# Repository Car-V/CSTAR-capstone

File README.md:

# CSTAR-capstone
Concrete Sounding Tool Automated Robot for EECE4792 Capstone 2

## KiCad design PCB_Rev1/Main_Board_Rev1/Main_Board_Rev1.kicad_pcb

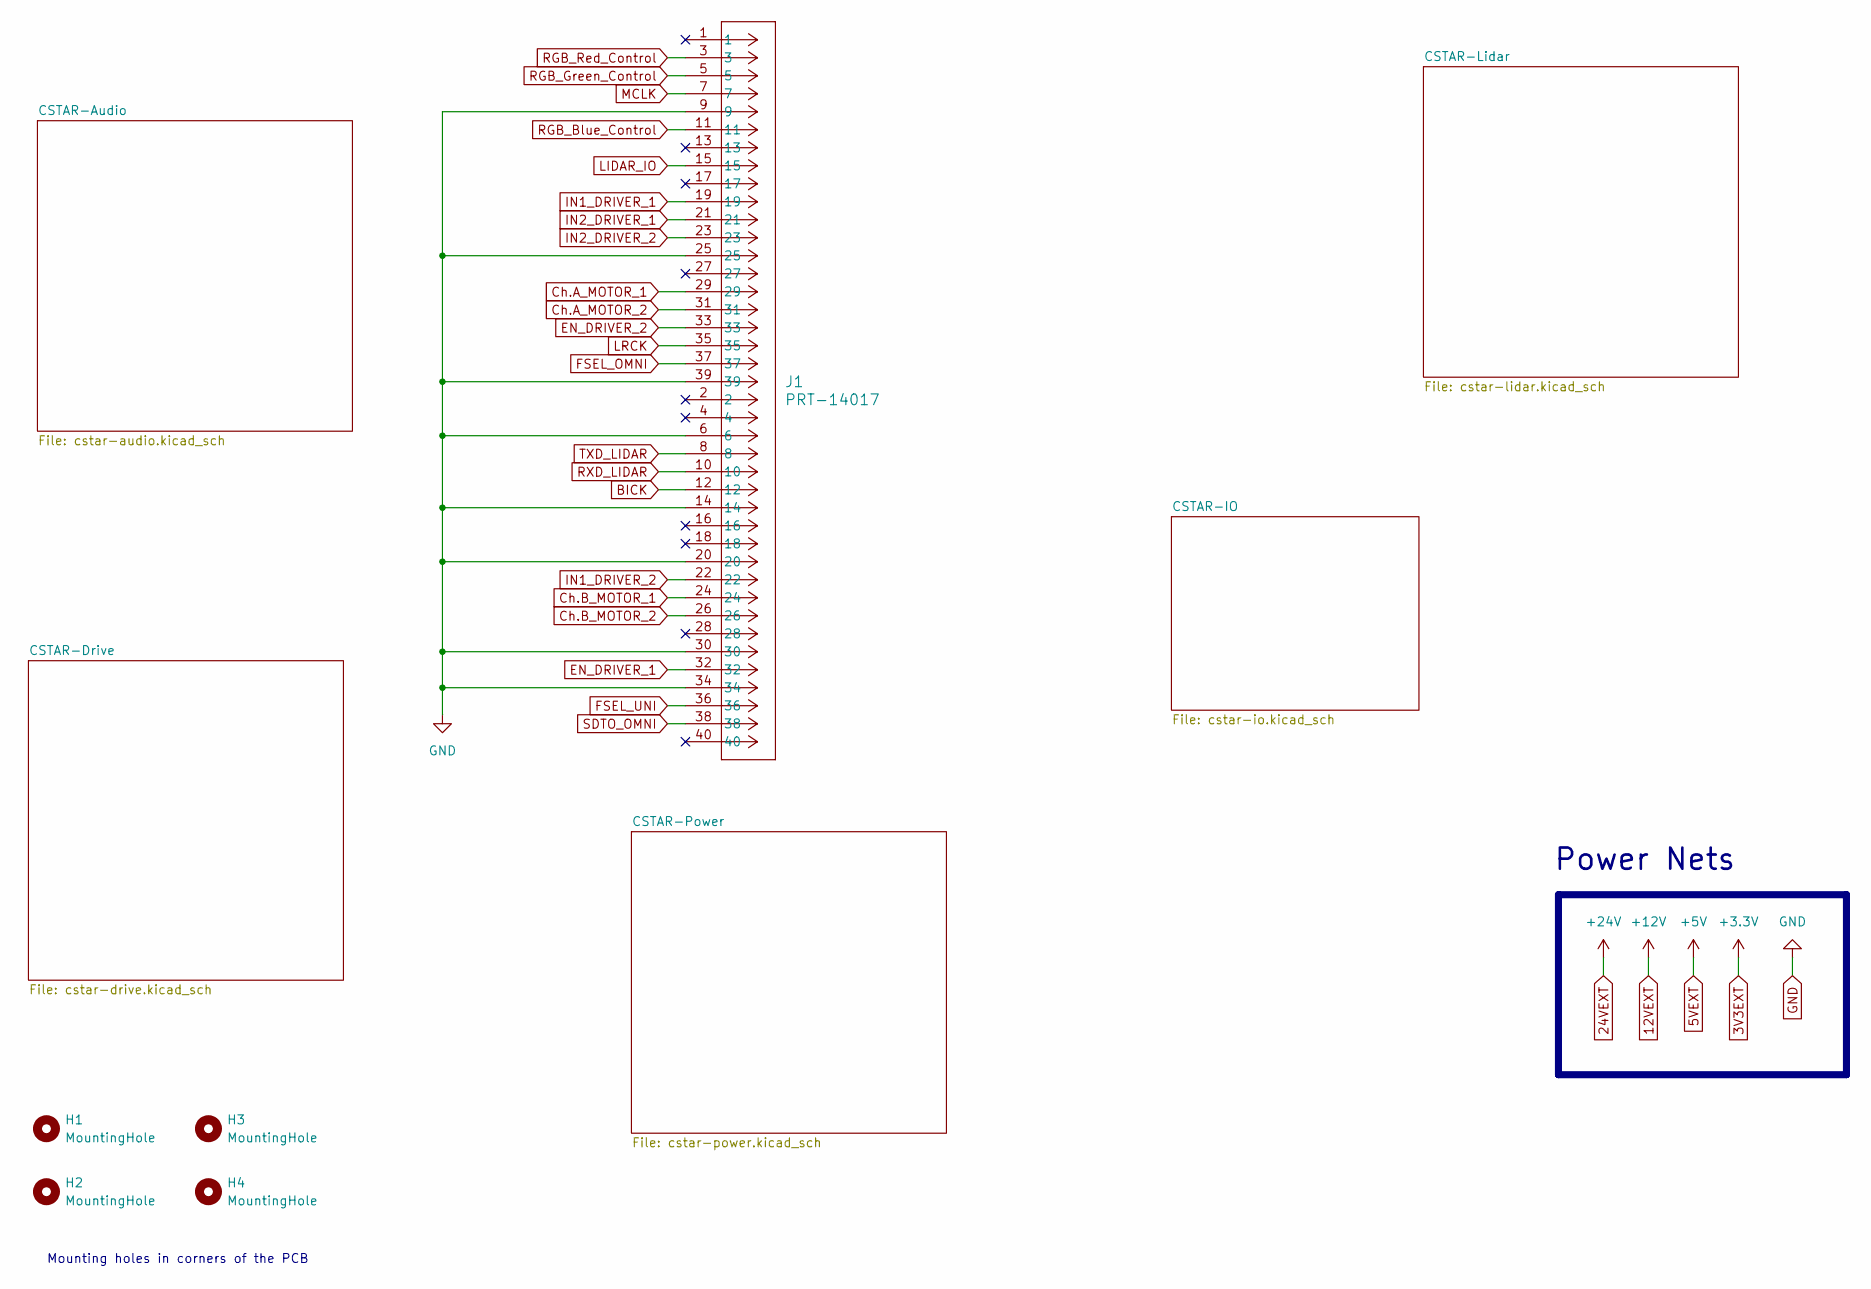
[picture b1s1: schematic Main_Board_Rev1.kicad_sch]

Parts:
H1, H2, H3, H4: MountingHole; MountingHole_5.3mm_M5_DIN965_Pad
J1: PRT-14017; RPiConnector; LCSC C2859067

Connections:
BICK: J1.12; also elsewhere on the board
Ch.A_MOTOR_1: J1.29; also elsewhere on the board
Ch.A_MOTOR_2: J1.31; also elsewhere on the board
Ch.B_MOTOR_1: J1.24; also elsewhere on the board
Ch.B_MOTOR_2: J1.26; also elsewhere on the board
EN_DRIVER_1: J1.32; also elsewhere on the board
EN_DRIVER_2: J1.33; also elsewhere on the board
FSEL_OMNI: J1.37; also elsewhere on the board
FSEL_UNI: J1.36; also elsewhere on the board
GND: J1.6, J1.9, J1.14, J1.20, J1.25, J1.30, J1.34, J1.39; also elsewhere on the board
IN1_DRIVER_1: J1.19; also elsewhere on the board
IN1_DRIVER_2: J1.22; also elsewhere on the board
IN2_DRIVER_1: J1.21; also elsewhere on the board
IN2_DRIVER_2: J1.23; also elsewhere on the board
LIDAR_IO: J1.15; also elsewhere on the board
LRCK: J1.35; also elsewhere on the board
MCLK: J1.7; also elsewhere on the board
RGB_Blue_Control: J1.11; also elsewhere on the board
RGB_Green_Control: J1.5; also elsewhere on the board
RGB_Red_Control: J1.3; also elsewhere on the board
RXD_LIDAR: J1.10; also elsewhere on the board
SDTO_OMNI: J1.38; also elsewhere on the board
TXD_LIDAR: J1.8; also elsewhere on the board

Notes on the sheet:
Power Nets
Mounting holes in corners of the PCB

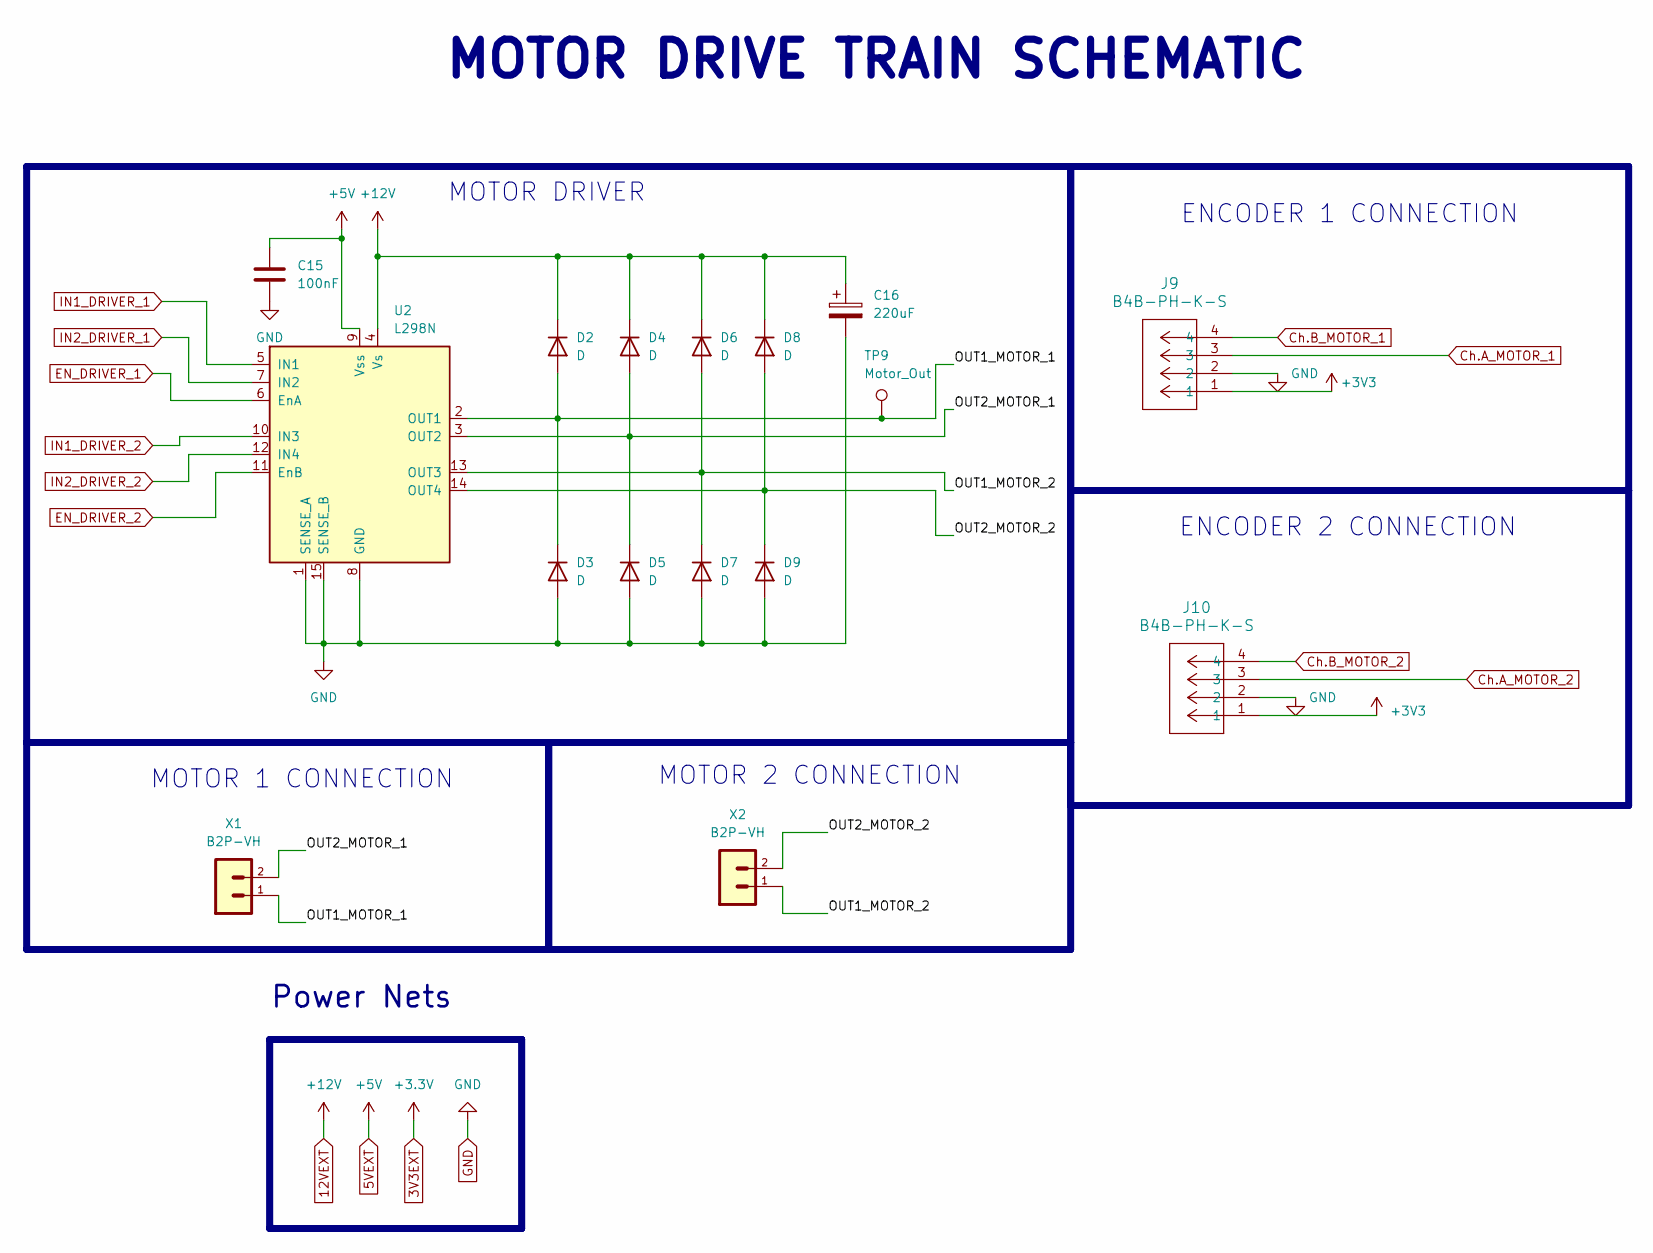
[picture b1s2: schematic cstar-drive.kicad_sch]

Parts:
C15: 100nF; C_0805_2012Metric; LCSC C520083
C16: 220uF; Cap_Polarized_220uF; LCSC C88729
D2, D3, D4, D5, D6, D7, D8, D9: D; Diode_1N4007; LCSC C516593
J9, J10: B4B-PH-K-S; B4B_PH_K_S; LCSC C305985
TP9: Motor_Out; TestPoint_Pad_D2.0mm
U2: L298N; TO-220-15_P2.54x2.54mm_StaggerOdd_Lead4.58mm_Vertical; LCSC C19922
X1, X2: B2P-VH; LCSC C160315

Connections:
5VEXT: C15.1, U2.9 (Vss); also elsewhere on the board
12VEXT: C16.1, D2.1 (K), D4.1 (K), D6.1 (K), D8.1 (K), U2.4 (Vs); also elsewhere on the board
+3V3: J9.1, J10.1; also elsewhere on the board
/CSTAR-Drive/OUT1_MOTOR_1: D2.2 (A), D3.1 (K), TP9.1, U2.2 (OUT1), X1.1
/CSTAR-Drive/OUT1_MOTOR_2: D6.2 (A), D7.1 (K), U2.13 (OUT3), X2.1
/CSTAR-Drive/OUT2_MOTOR_1: D4.2 (A), D5.1 (K), U2.3 (OUT2), X1.2
/CSTAR-Drive/OUT2_MOTOR_2: D8.2 (A), D9.1 (K), U2.14 (OUT4), X2.2
Ch.A_MOTOR_1: J9.3; also elsewhere on the board
Ch.A_MOTOR_2: J10.3; also elsewhere on the board
Ch.B_MOTOR_1: J9.4; also elsewhere on the board
Ch.B_MOTOR_2: J10.4; also elsewhere on the board
EN_DRIVER_1: U2.6 (EnA); also elsewhere on the board
EN_DRIVER_2: U2.11 (EnB); also elsewhere on the board
GND: C15.2, C16.2, D3.2 (A), D5.2 (A), D7.2 (A), D9.2 (A), J9.2, J10.2, U2.1 (SENSE_A), U2.8 (GND), U2.15 (SENSE_B); also elsewhere on the board
IN1_DRIVER_1: U2.5 (IN1); also elsewhere on the board
IN1_DRIVER_2: U2.10 (IN3); also elsewhere on the board
IN2_DRIVER_1: U2.7 (IN2); also elsewhere on the board
IN2_DRIVER_2: U2.12 (IN4); also elsewhere on the board

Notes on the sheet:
MOTOR 2 CONNECTION
Power Nets
MOTOR 1 CONNECTION
MOTOR DRIVER
ENCODER 1 CONNECTION
ENCODER 2 CONNECTION
MOTOR DRIVE TRAIN SCHEMATIC

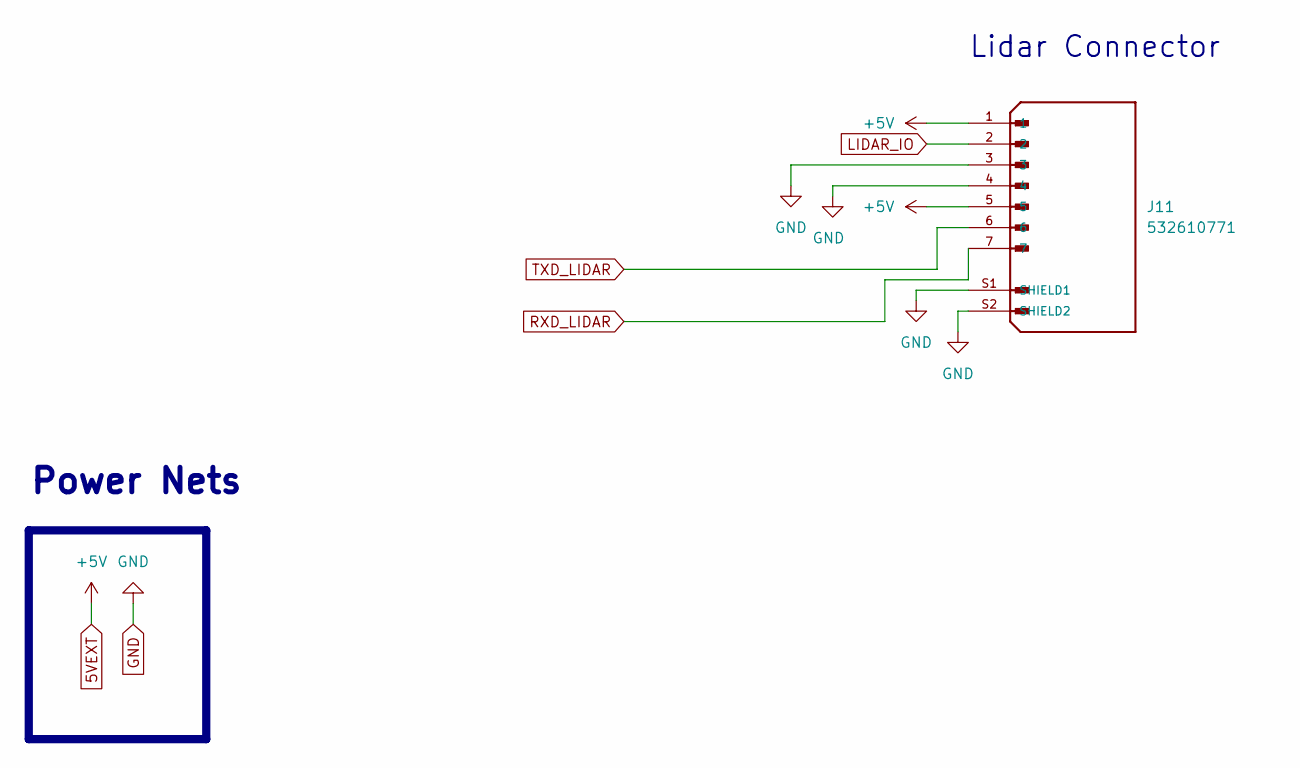
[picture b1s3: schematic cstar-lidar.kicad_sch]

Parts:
J11: 532610771; MOLEX_connector; PARTREV J; DigiKey_Part_Number WM7625TR-ND

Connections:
5VEXT: J11.1, J11.5; also elsewhere on the board
GND: J11.3, J11.4, J11.S1 (SHIELD1), J11.S2 (SHIELD2); also elsewhere on the board
LIDAR_IO: J11.2; also elsewhere on the board
RXD_LIDAR: J11.7; also elsewhere on the board
TXD_LIDAR: J11.6; also elsewhere on the board

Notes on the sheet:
Lidar Connector
Power Nets

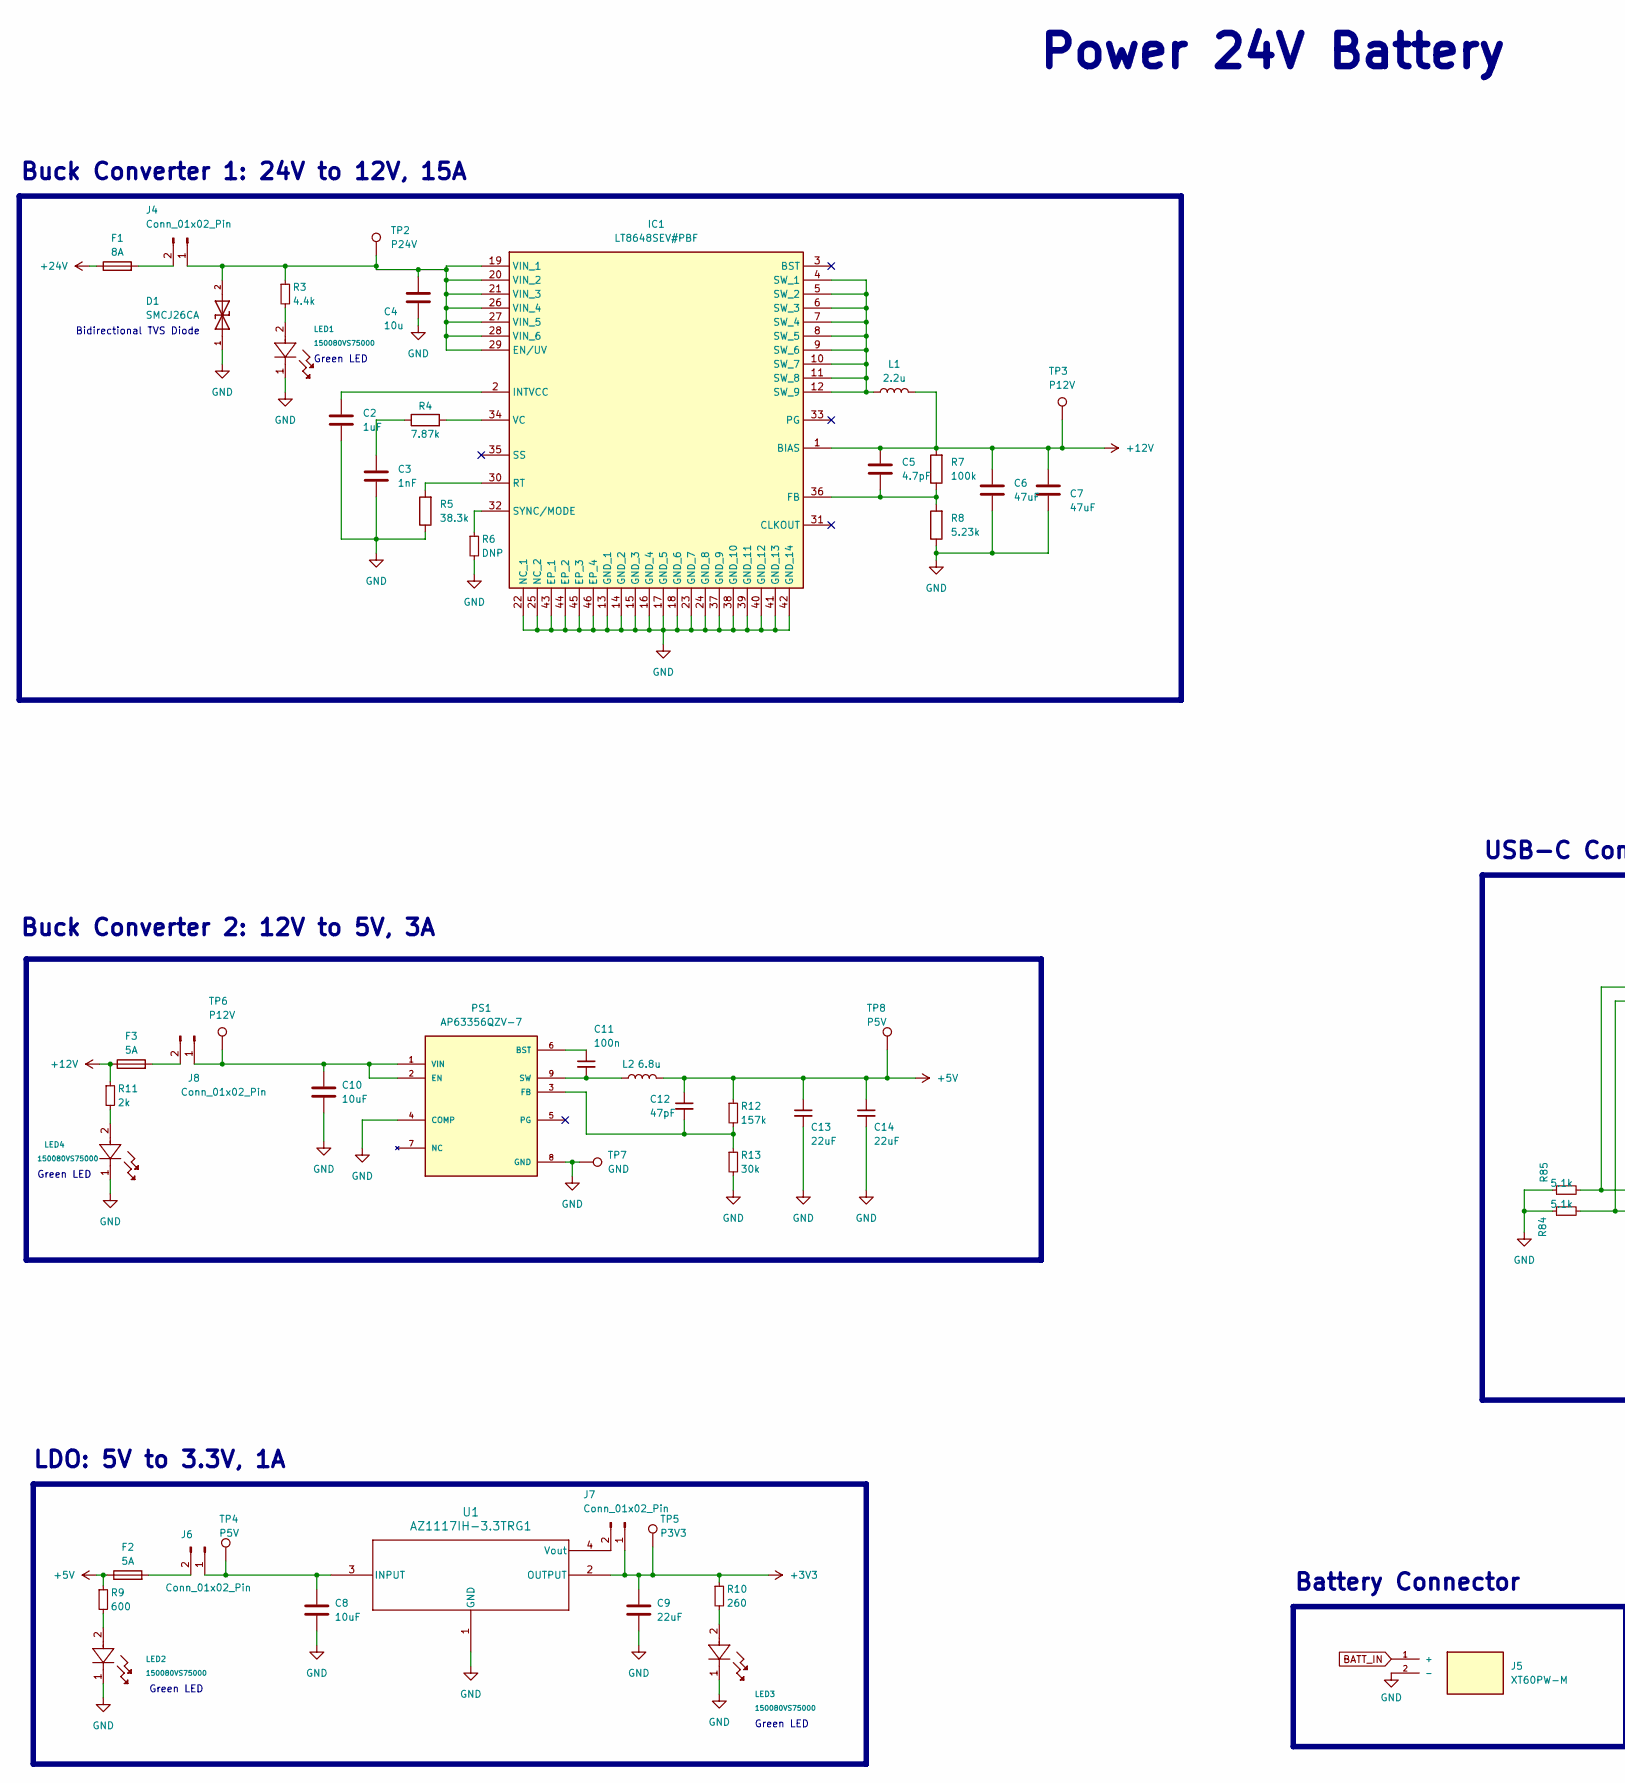
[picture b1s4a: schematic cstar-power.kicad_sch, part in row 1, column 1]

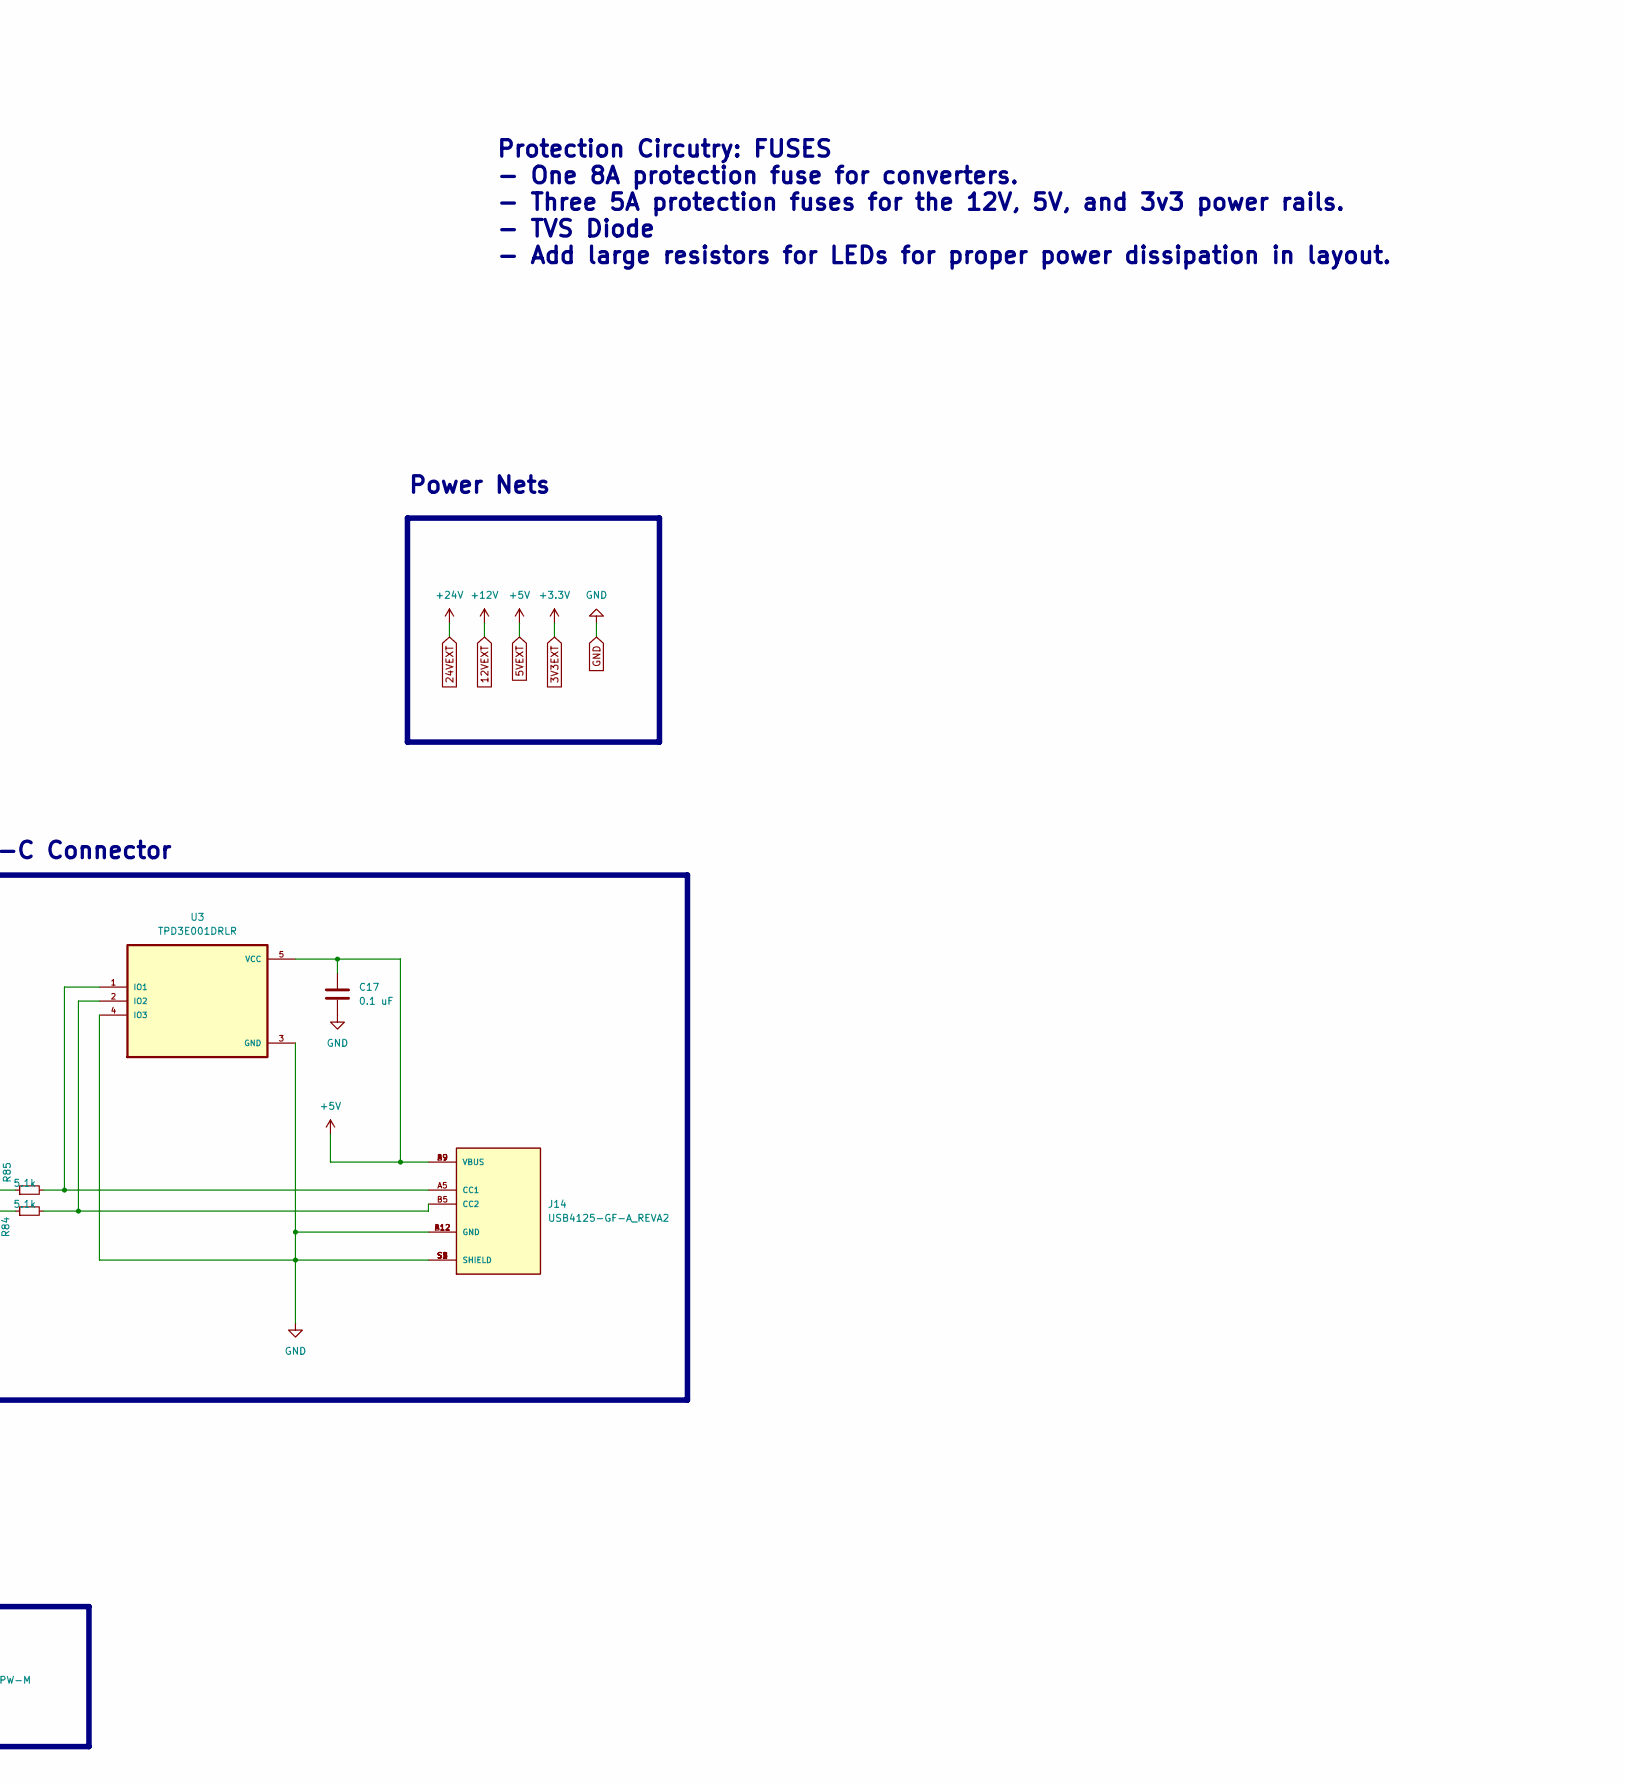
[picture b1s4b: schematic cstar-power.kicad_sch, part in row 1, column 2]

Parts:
C2: 1uF; C_0805_2012Metric; LCSC C116352
C3: 1nF; C_0805_2012Metric; LCSC C2167084
C4: 10u; C_0805_2012Metric; LCSC C2190942
C5: 4.7pF; C_0805_2012Metric; LCSC C527074
C6, C7: 47uF; C_1206_3216Metric; LCSC C2167787
C8, C10: 10uF; C_0805_2012Metric; LCSC C2190942
C9, C13, C14: 22uF; C_0805_2012Metric; LCSC C602037
C11: 100n; C_0805_2012Metric; LCSC C49678
C12: 47pF; C_0805_2012Metric; LCSC C107118
C17: 0.1 uF; C_0805_2012Metric; LCSC C49678
D1: SMCJ26CA; D1_Bi-dir; PARTREV 11/20/15; LCSC C151280
F1: 8A; Fuse_0805_2012Metric; LCSC C3158319
F2, F3: 5A; Fuse_0805_2012Metric; LCSC C3159342
IC1: LT8648SEV#PBF; Buck_1; Mouser Part Number 584-LT8648SEV#PBF
J4, J6, J7, J8: Conn_01x02_Pin; PinHeader_1x02_P2.54mm_Vertical; LCSC C5828287
J5: XT60PW-M; AMASS_XT60PW-M_1x02_P7.20mm_Horizontal; LCSC C98732
J14: USB4125-GF-A_REVA2; GCT_USB4125-GF-A_REVA2; PARTREV Rev A2; LCSC C5246813
L1: 2.2u; L_0805_2012Metric; LCSC C540967
L2: 6.8u; L_0805_2012Metric; LCSC C844992
LED1, LED2, LED3, LED4: 150080VS75000; LED_0805_2012Metric
PS1: AP63356QZV-7; Buck_2; PARTREV 1-2; LCSC C3194571
R3: 4.4k; R_0805_2012Metric; LCSC C273997
R4: 7.87k; R_0805_2012Metric; LCSC C273910
R5: 38.3k; R_0805_2012Metric; LCSC C273970
R6: DNP; R_0805_2012Metric
R7: 100k; R_0805_2012Metric; LCSC C96346
R8: 5.23k; R_0805_2012Metric; LCSC C274009
R9: 600; R_0805_2012Metric; LCSC C137416
R10: 260; R_0805_2012Metric; LCSC C483083
R11: 2k; R_0805_2012Metric; LCSC C273808
R12: 157k; R_0805_2012Metric; LCSC C273954
R13: 30k; R_0805_2012Metric; LCSC C126352
R84, R85: 5.1k; R_0805_2012Metric; LCSC C105874
TP2: P24V; TestPoint_Pad_D2.0mm
TP3, TP6: P12V; TestPoint_Pad_D2.0mm
TP4, TP8: P5V; TestPoint_Pad_D2.0mm
TP5: P3V3; TestPoint_Pad_D2.0mm
TP7: GND; TestPoint_Pad_D2.0mm
U1: AZ1117IH-3.3TRG1; LDO; LCSC C108495
U3: TPD3E001DRLR; USBC_ESD_Protection; LCSC C470828

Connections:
5VEXT: C12.1, C13.1, C14.1, C17.1, F2.1, J14.A9 (VBUS), J14.B9 (VBUS), L2.2, R9.1, R12.1, TP8.1, U3.5 (VCC); also elsewhere on the board
12VEXT: C5.1, C6.1, C7.1, F3.1, IC1.1 (BIAS), L1.2, R7.2, R11.1, TP3.1; also elsewhere on the board
24VEXT: F1.1; also elsewhere on the board
+3V3: C9.1, J7.1, R10.1, TP5.1, U1.2 (OUTPUT); also elsewhere on the board
BATT_IN: J5.1 (+); also elsewhere on the board
GND: C2.2, C3.2, C4.2, C6.2, C7.2, C8.2, C9.2, C10.2, C13.2, C14.2, C17.2, D1.1, IC1.13 (GND_1), IC1.14 (GND_2), IC1.15 (GND_3), IC1.16 (GND_4), IC1.17 (GND_5), IC1.18 (GND_6), IC1.22 (NC_1), IC1.23 (GND_7), IC1.24 (GND_8), IC1.25 (NC_2), IC1.37 (GND_9), IC1.38 (GND_10), IC1.39 (GND_11), IC1.40 (GND_12), IC1.41 (GND_13), IC1.42 (GND_14), IC1.43 (EP_1), IC1.44 (EP_2), IC1.45 (EP_3), IC1.46 (EP_4), J5.2 (-), J14.A12 (GND), J14.B12 (GND), J14.S1 (SHIELD), J14.S2 (SHIELD), J14.S3 (SHIELD), J14.S4 (SHIELD), LED1.1, LED2.1, LED3.1, LED4.1, PS1.4 (COMP), PS1.8 (GND), R5.1, R6.2, R8.1, R13.2, R84.1, R85.1, TP7.1, U1.1 (GND), U3.3 (GND), U3.4 (IO3); also elsewhere on the board
unnamed: C3.1, R4.1
unnamed: C4.1, D1.2, IC1.19 (VIN_1), IC1.20 (VIN_2), IC1.21 (VIN_3), IC1.26 (VIN_4), IC1.27 (VIN_5), IC1.28 (VIN_6), IC1.29 (EN/UV), J4.1, R3.1, TP2.1
unnamed: C5.2, IC1.36 (FB), R7.1, R8.2
unnamed: C2.1, IC1.2 (INTVCC)
unnamed: IC1.30 (RT), R5.2
unnamed: IC1.4 (SW_1), IC1.5 (SW_2), IC1.6 (SW_3), IC1.7 (SW_4), IC1.8 (SW_5), IC1.9 (SW_6), IC1.10 (SW_7), IC1.11 (SW_8), IC1.12 (SW_9), L1.1
unnamed: IC1.32 (SYNC/MODE), R6.1
unnamed: IC1.34 (VC), R4.2
unnamed: F1.2, J4.2
unnamed: C8.1, J6.1, TP4.1, U1.3 (INPUT)
unnamed: F2.2, J6.2
unnamed: J7.2, U1.4 (Vout)
unnamed: C10.1, J8.1, PS1.1 (VIN), PS1.2 (EN), TP6.1
unnamed: F3.2, J8.2
unnamed: J14.A5 (CC1), R85.2, U3.1 (IO1)
unnamed: J14.B5 (CC2), R84.2, U3.2 (IO2)
unnamed: LED1.2, R3.2
unnamed: LED2.2, R9.2
unnamed: LED3.2, R10.2
unnamed: LED4.2, R11.2
unnamed: C11.1, PS1.6 (BST)
unnamed: C12.2, PS1.3 (FB), R12.2, R13.1
unnamed: C11.2, L2.1, PS1.9 (SW)

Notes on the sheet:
Power Nets
Green LED
LDO: 5V to 3.3V, 1A
Protection Circutry: FUSES - One 8A protection fuse for converters. - Three 5A protection fuses for the 12V, 5V, and 3v3 power rails. - TVS Diode - Add large resistors for LEDs for proper power dissipation in layout.
Bidirectional TVS Diode
Battery Connector
Power 24V Battery
Buck Converter 2: 12V to 5V, 3A
USB-C Connector
Buck Converter 1: 24V to 12V, 15A

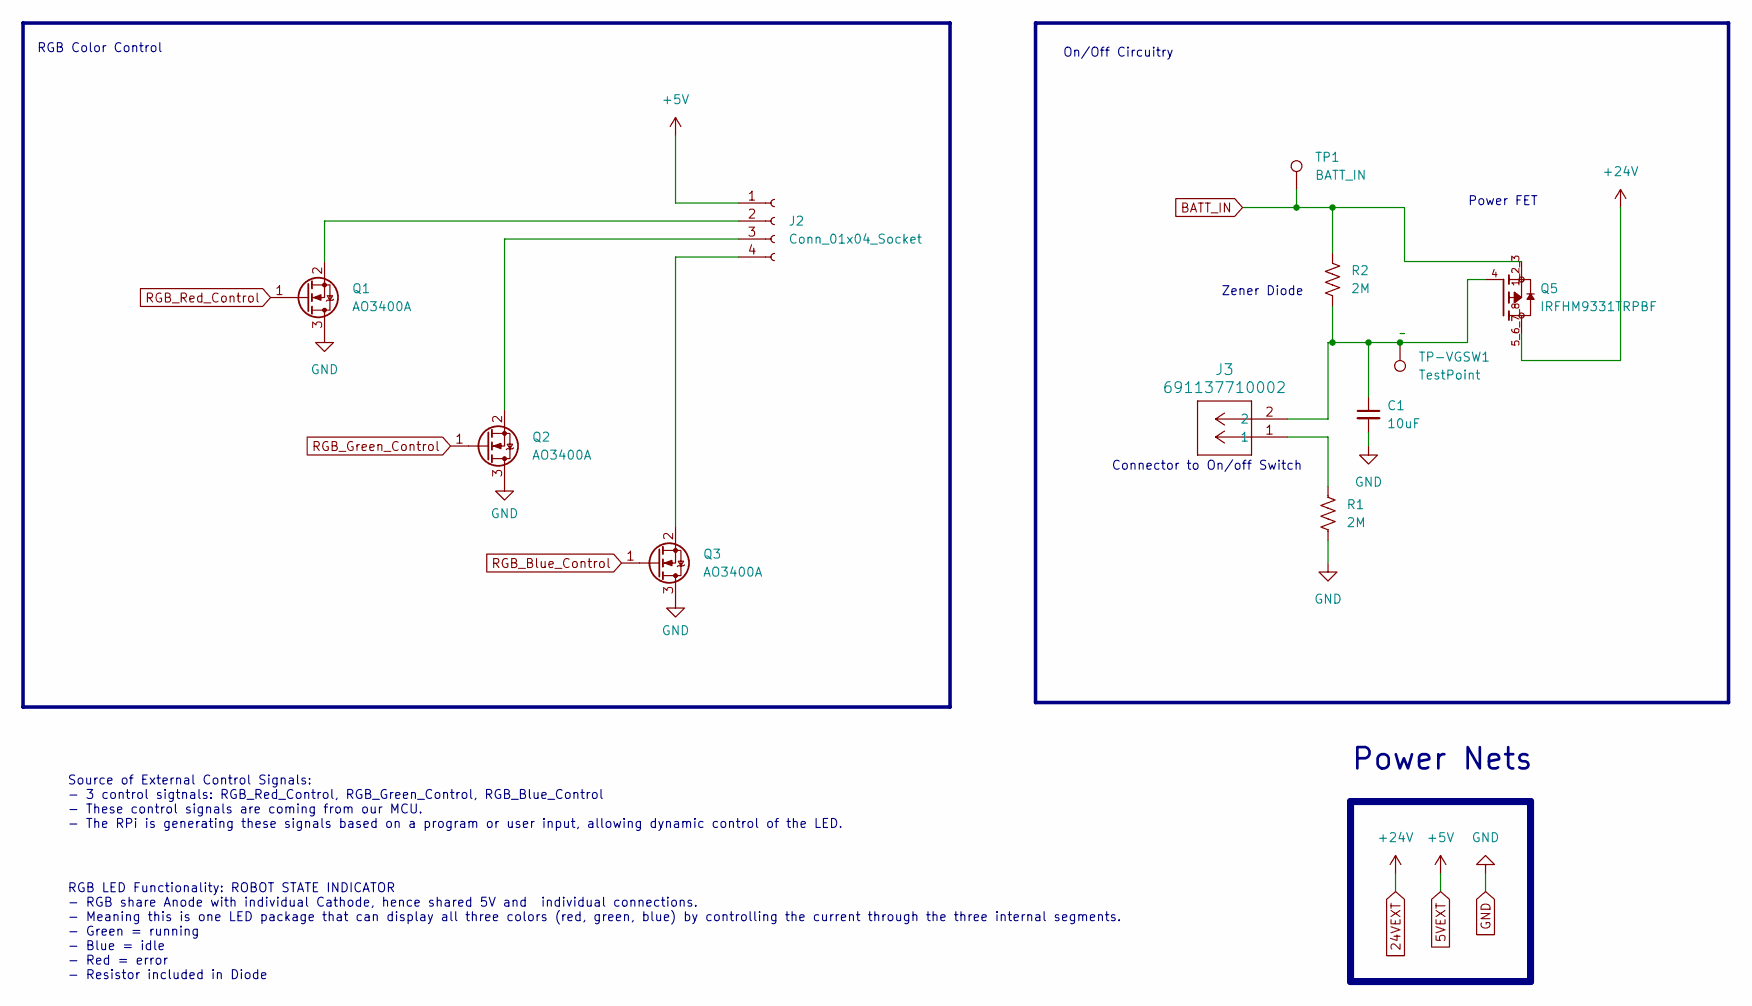
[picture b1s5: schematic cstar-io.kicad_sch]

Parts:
C1: 10uF; C_0805_2012Metric; LCSC C2190942
J2: Conn_01x04_Socket; EncoderConn; LCSC C566011
J3: 691137710002; 691137710002-2CONN; LCSC C3819953
Q1, Q2, Q3: AO3400A; RGB-FETS; LCSC C20917
Q5: IRFHM9331TRPBF; TRANS_IRFHM9331TRPBF; PARTREV December 16, 2013; LCSC C148156
R1, R2: 2M; R_0805_2012Metric; LCSC C114532
TP1: BATT_IN; TestPoint_Pad_D2.0mm
TP-VGSW1: TestPoint; TestPoint_Pad_D2.0mm

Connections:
5VEXT: J2.1; also elsewhere on the board
24VEXT: Q5.5_6_7_8; also elsewhere on the board
BATT_IN: Q5.1_2_3, R2.1, TP1.1; also elsewhere on the board
GND: C1.2, Q1.3 (D), Q2.3 (D), Q3.3 (D), R1.2; also elsewhere on the board
unnamed: C1.1, J3.2, Q5.4, R2.2, TP-VGSW1.1
unnamed: J2.2, Q1.2 (S)
unnamed: J2.3, Q2.2 (S)
unnamed: J2.4, Q3.2 (S)
unnamed: J3.1, R1.1
RGB_Blue_Control: Q3.1 (G); also elsewhere on the board
RGB_Green_Control: Q2.1 (G); also elsewhere on the board
RGB_Red_Control: Q1.1 (G); also elsewhere on the board

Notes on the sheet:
Zener Diode
RGB LED Functionality: ROBOT STATE INDICATOR - RGB share Anode with individual Cathode, hence shared 5V and individual connections. - Meaning this is one LED package that can display all three colors (red, green, blue) by controlling the current through the three internal segments. - Green = runnin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
Source of External Control Signals: - 3 control sigtnals: RGB_Red_Control, RGB_Green_Control, RGB_Blue_Control - These control signals are coming from our MCU. - The RPi is generating these signals based on a program or user input, allowing dynamic control of the LED.
Power FET
Connector to On/off Switch
On/Off Circuitry
RGB Color Control
Power Nets

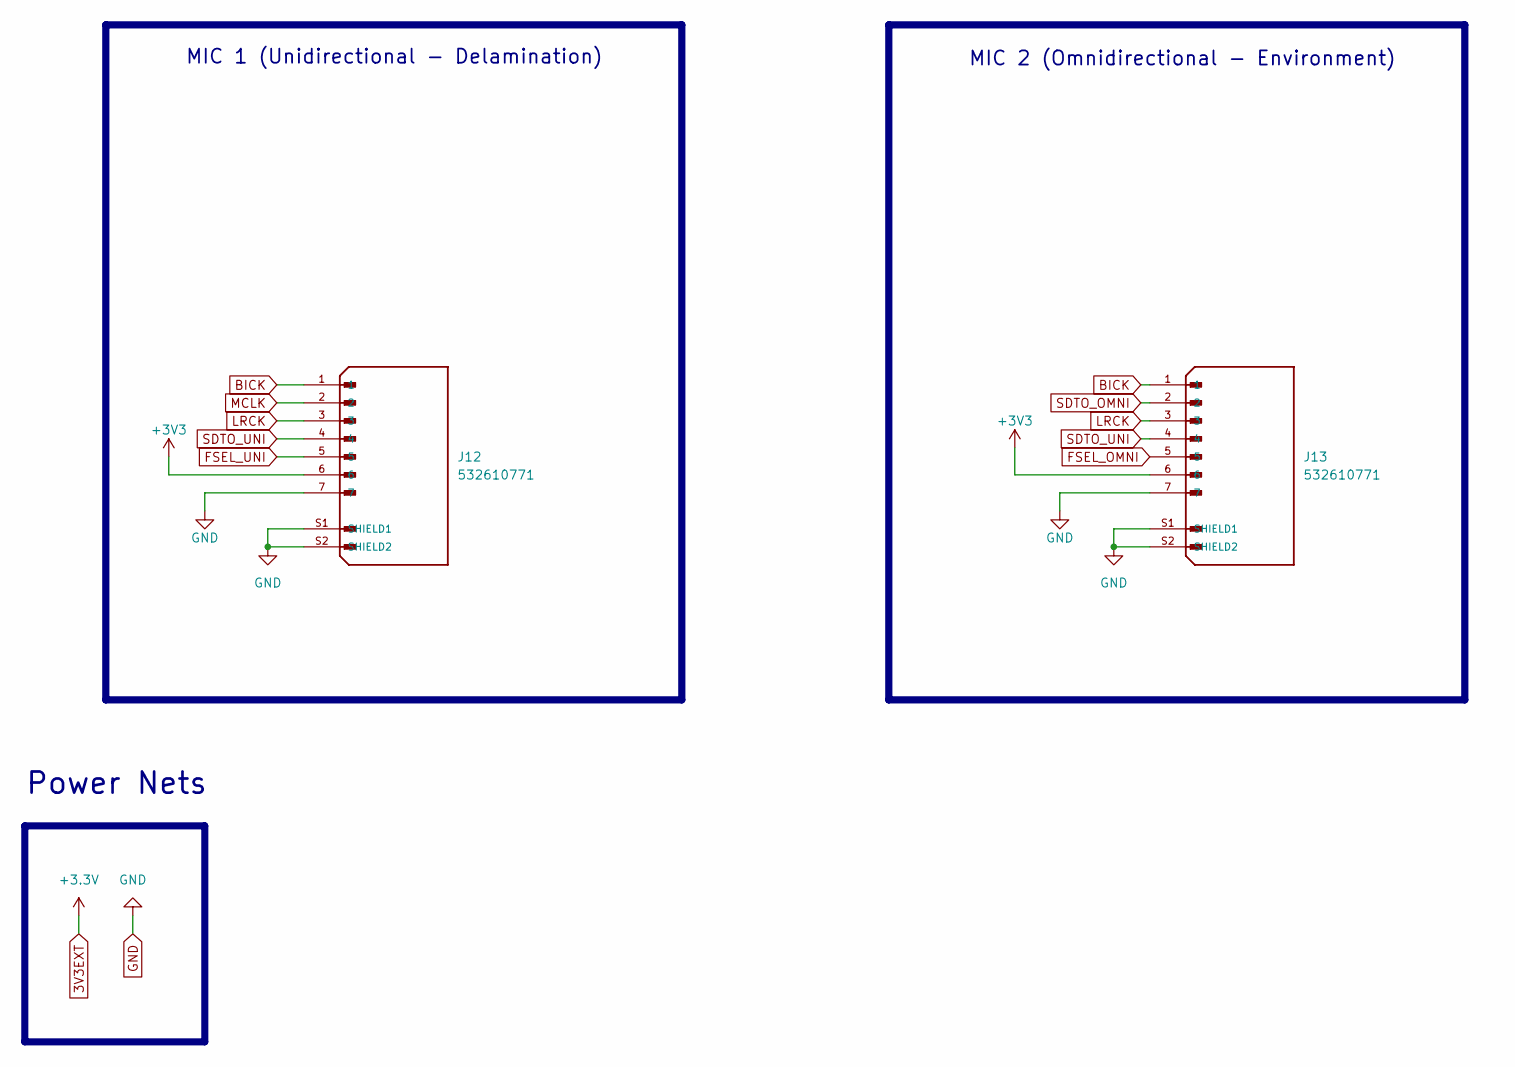
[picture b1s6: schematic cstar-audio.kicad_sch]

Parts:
J12, J13: 532610771; MOLEX_connector; PARTREV J; DigiKey_Part_Number WM7625TR-ND

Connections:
+3V3: J12.6, J13.6; also elsewhere on the board
BICK: J12.1, J13.1; also elsewhere on the board
FSEL_OMNI: J13.5; also elsewhere on the board
FSEL_UNI: J12.5; also elsewhere on the board
GND: J12.7, J12.S1 (SHIELD1), J12.S2 (SHIELD2), J13.7, J13.S1 (SHIELD1), J13.S2 (SHIELD2); also elsewhere on the board
LRCK: J12.3, J13.3; also elsewhere on the board
MCLK: J12.2; also elsewhere on the board
SDTO_OMNI: J13.2; also elsewhere on the board
SDTO_UNI: J12.4, J13.4

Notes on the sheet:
MIC 2 (Omnidirectional - Environment)
Power Nets
MIC 1 (Unidirectional - Delamination)

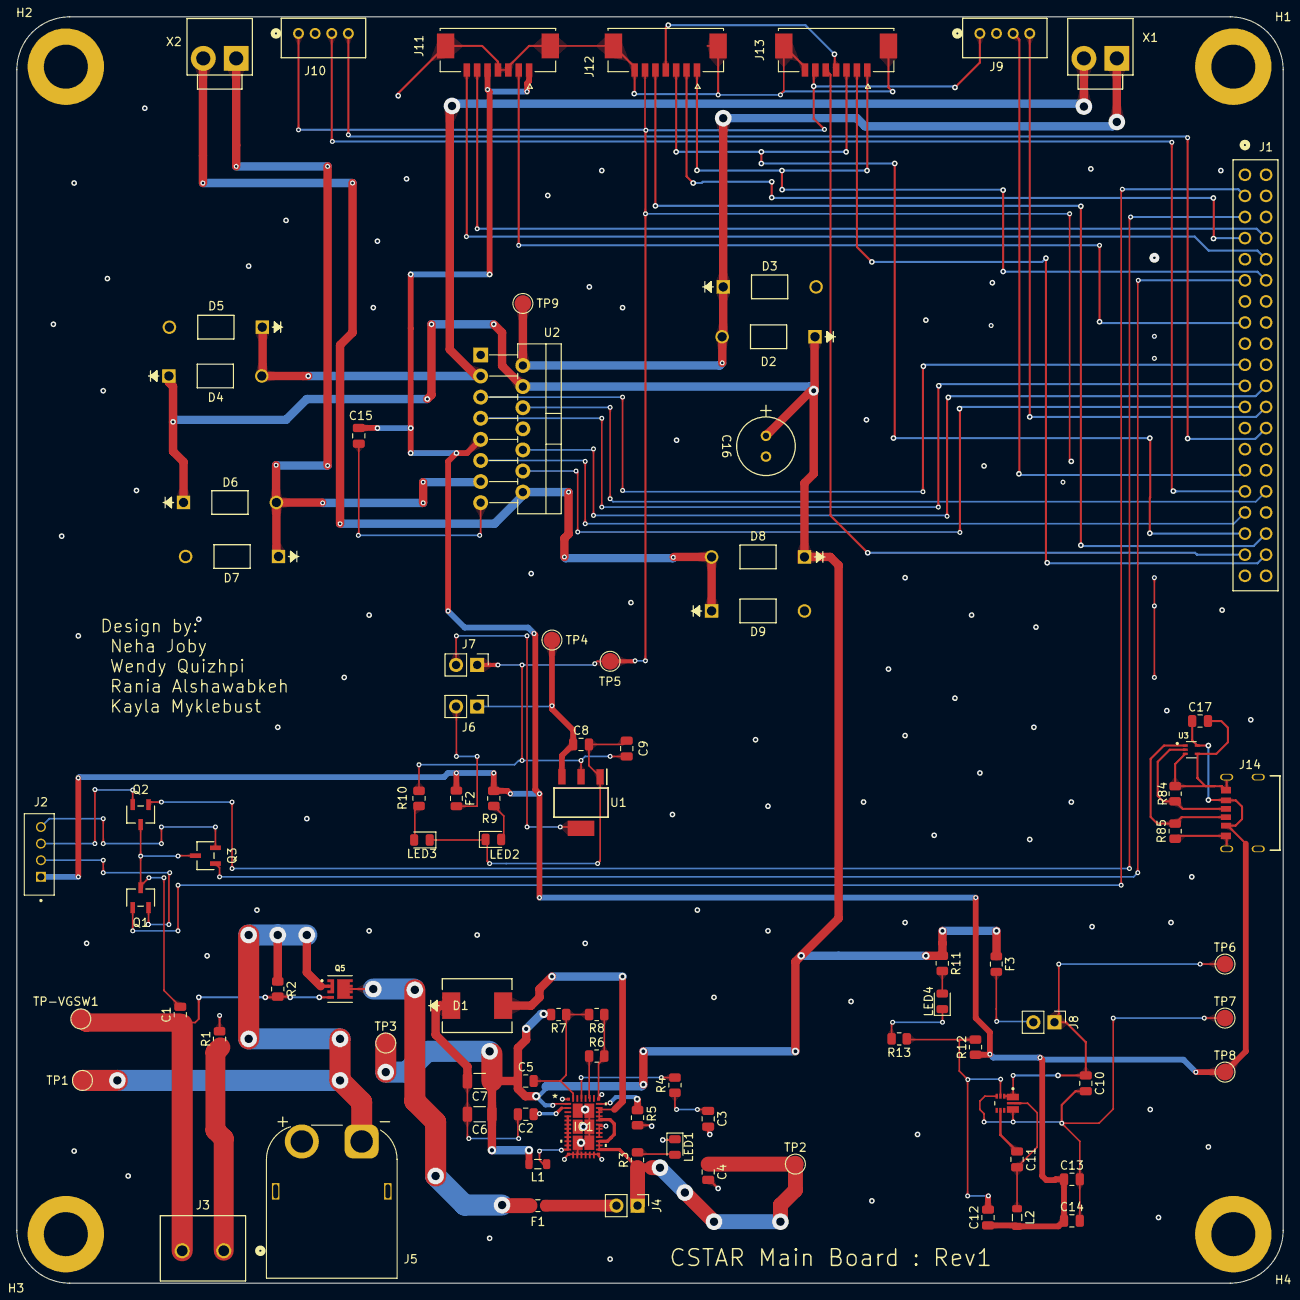
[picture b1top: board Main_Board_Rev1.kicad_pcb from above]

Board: 4 copper layers, 152.4 x 152.4 mm, 89 parts (0 on the bottom side), 61 nets.
